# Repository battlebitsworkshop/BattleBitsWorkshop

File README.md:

### Hi there 👋

Presentation:   
http://iboibelings.nl/BattleBitsWorkshop

Wiki:   
https://github.com/battlebitsworkshop/battlebitsworkshop/wiki
  
Assembly part one:   
https://github.com/battlebitsworkshop/battlebitsworkshop/wiki/Assembly-part-one

<!--
**battlebitsworkshop/BattleBitsWorkshop** is a ✨ _special_ ✨ repository because its `README.md` (this file) appears on your GitHub profile.

Here are some ideas to get you started:

- 🔭 I’m currently working on ...
- 🌱 I’m currently learning ...
- 👯 I’m looking to collaborate on ...
- 🤔 I’m looking for help with ...
- 💬 Ask me about ...
- 📫 How to reach me: ...
- 😄 Pronouns: ...
- ⚡ Fun fact: ...
-->

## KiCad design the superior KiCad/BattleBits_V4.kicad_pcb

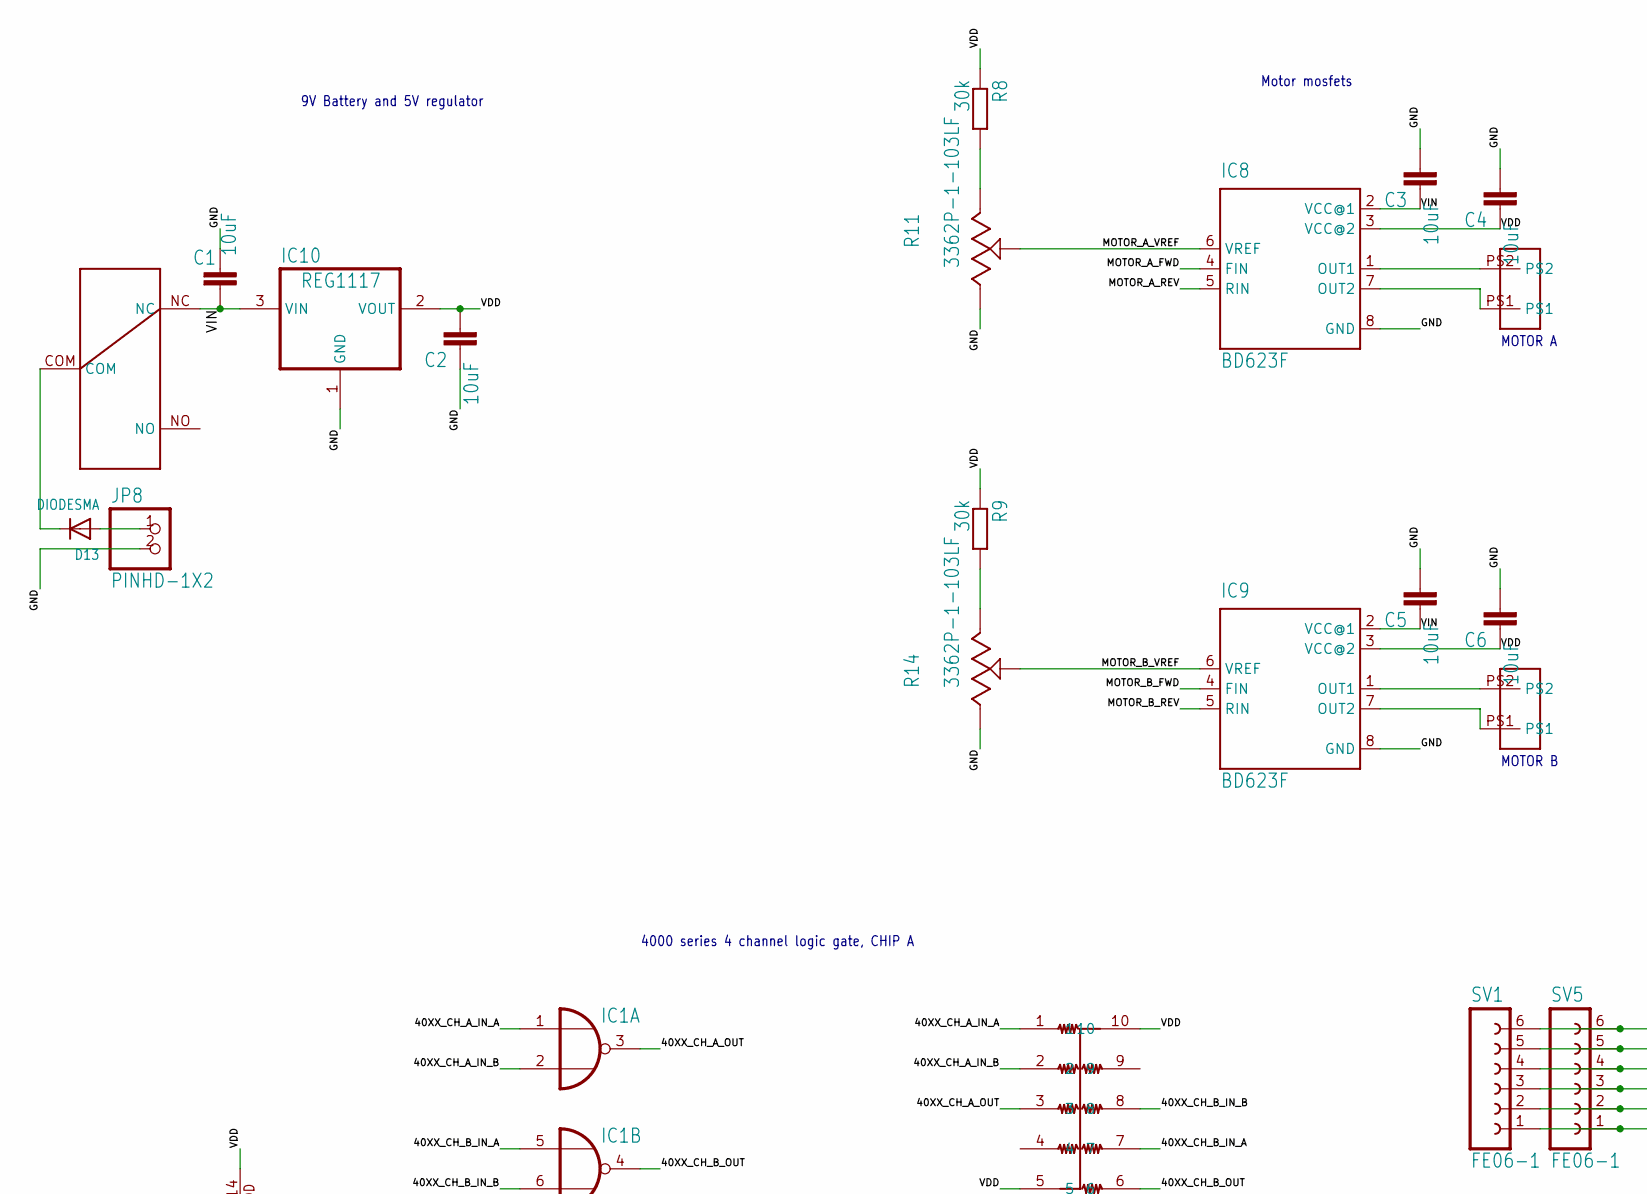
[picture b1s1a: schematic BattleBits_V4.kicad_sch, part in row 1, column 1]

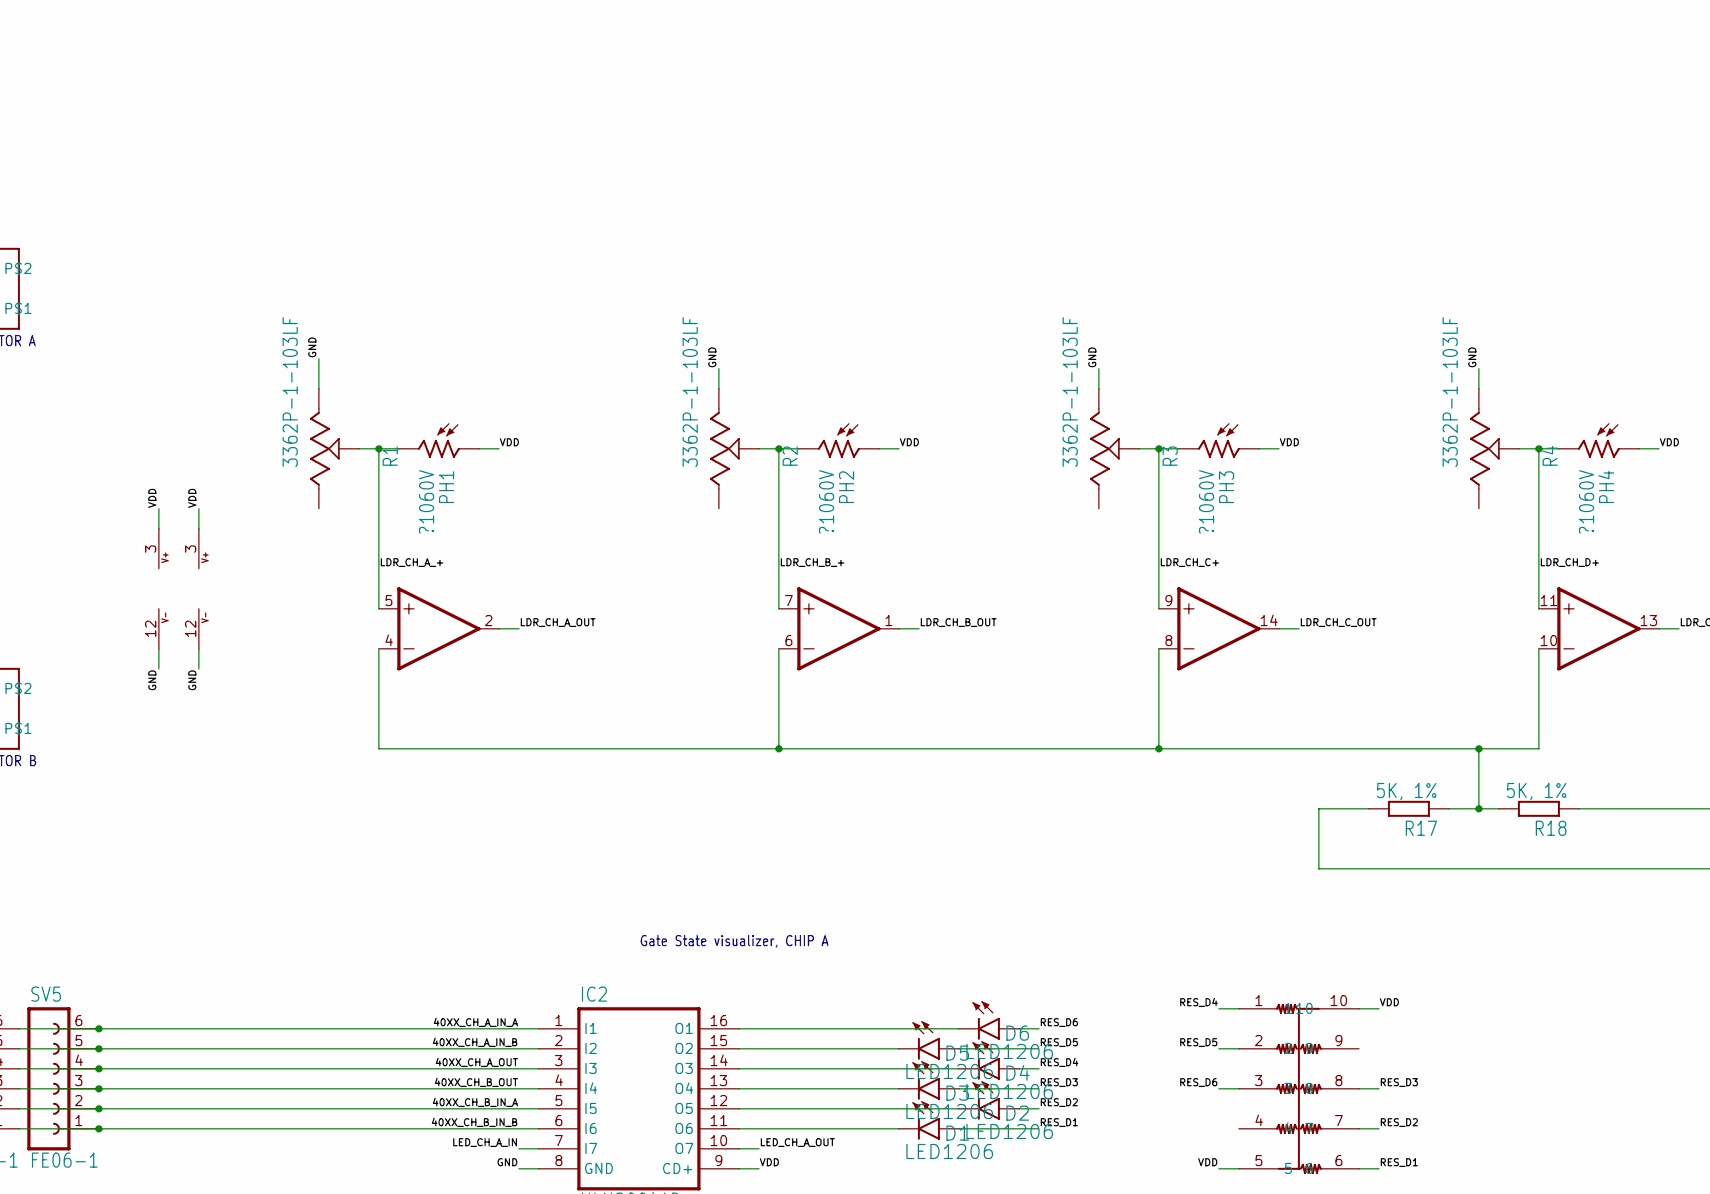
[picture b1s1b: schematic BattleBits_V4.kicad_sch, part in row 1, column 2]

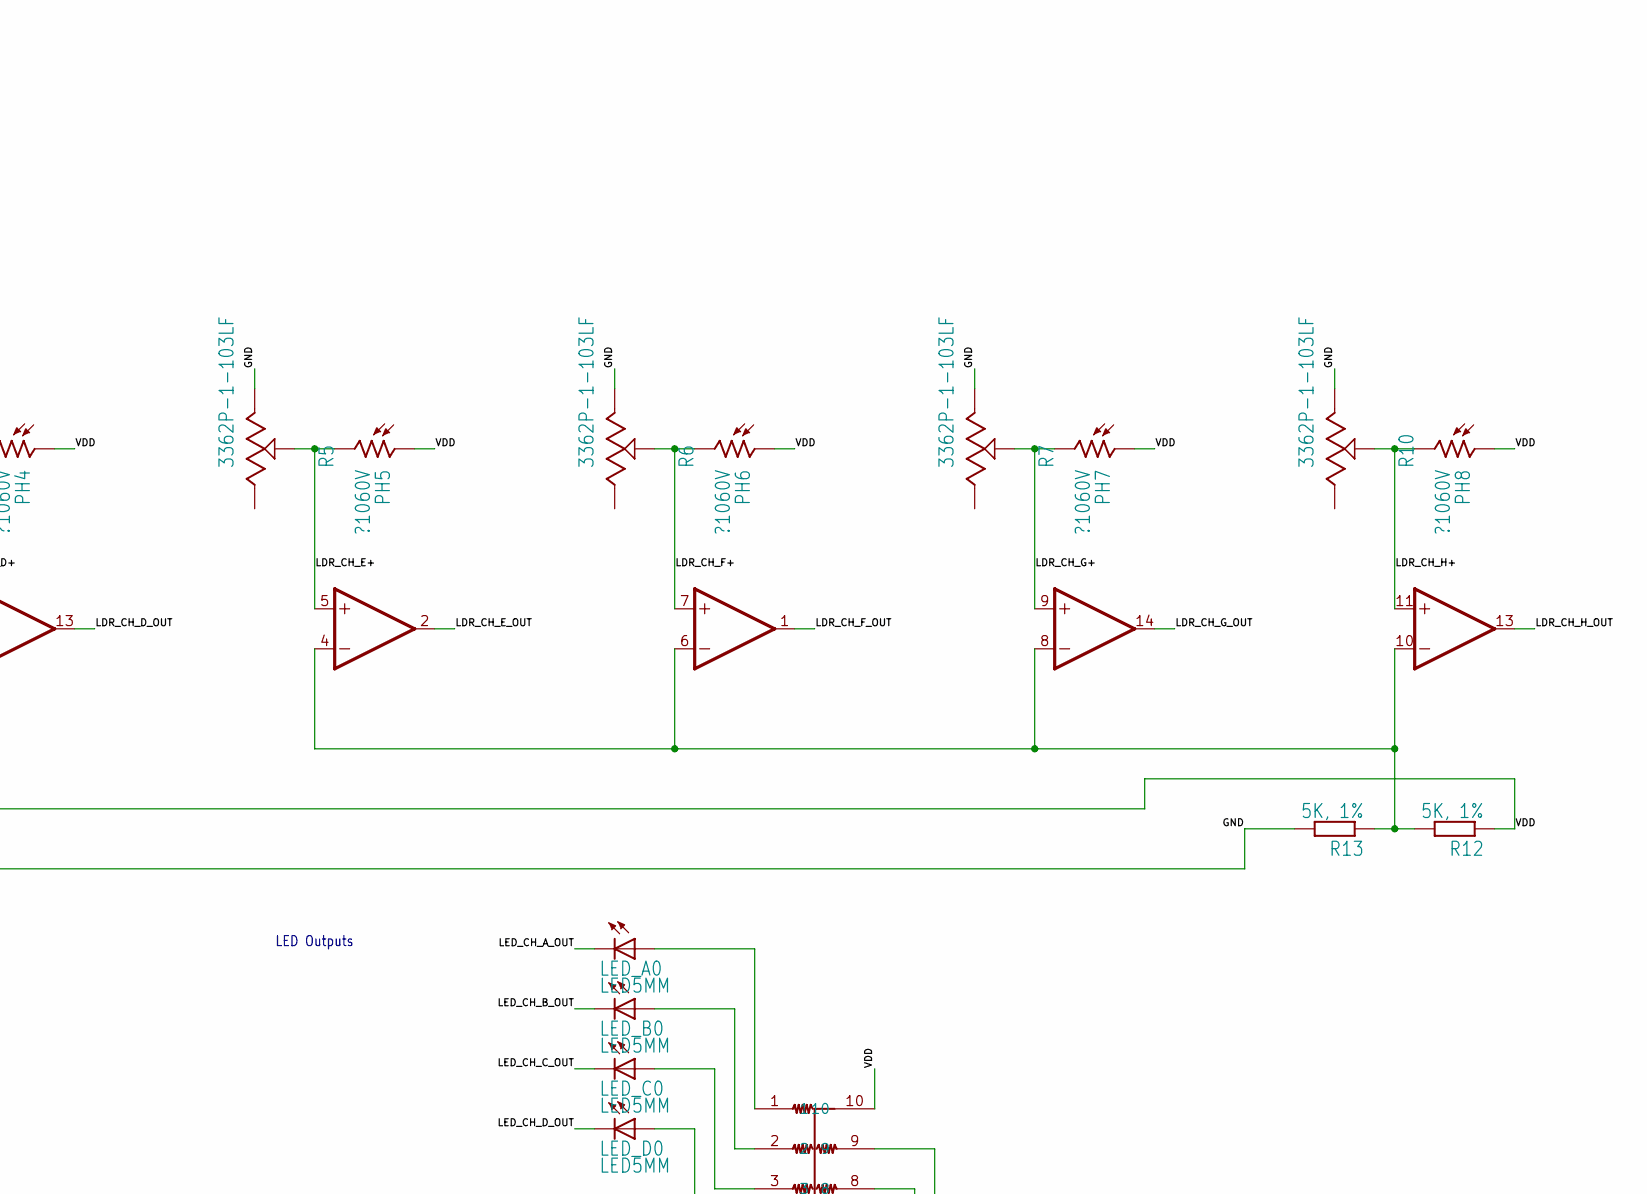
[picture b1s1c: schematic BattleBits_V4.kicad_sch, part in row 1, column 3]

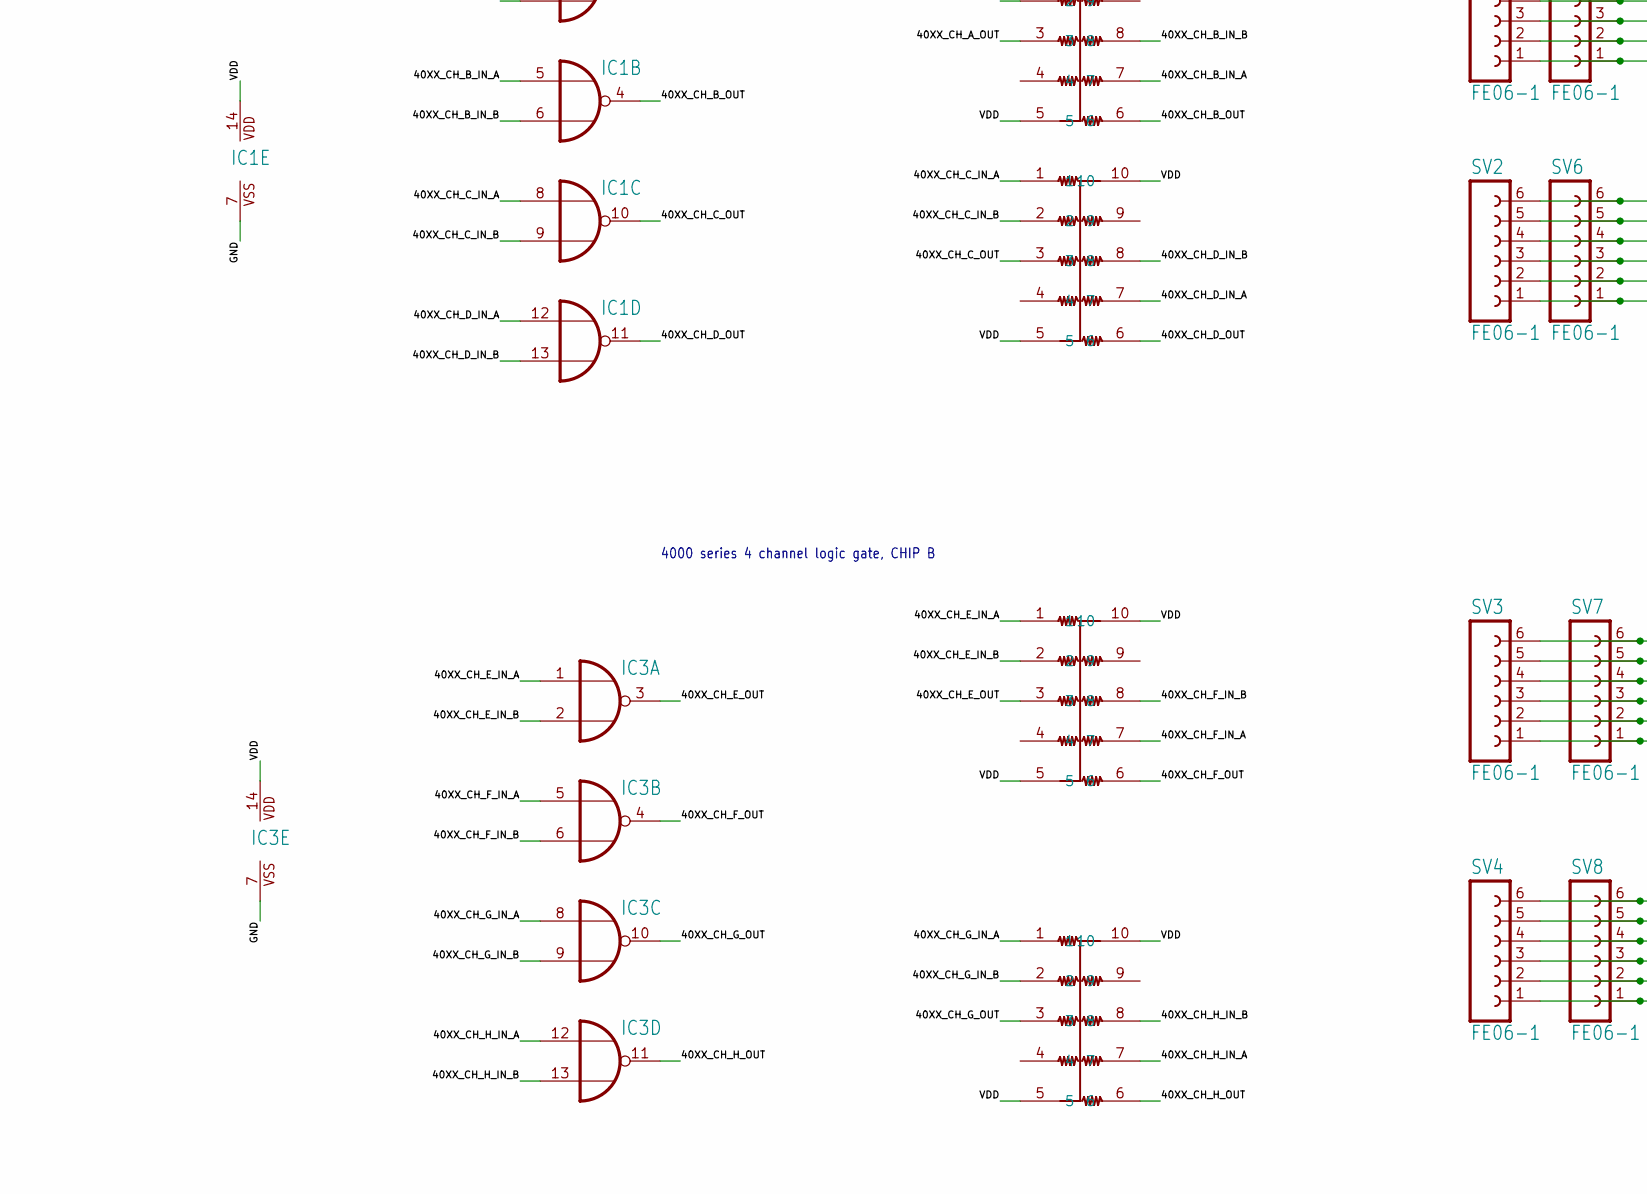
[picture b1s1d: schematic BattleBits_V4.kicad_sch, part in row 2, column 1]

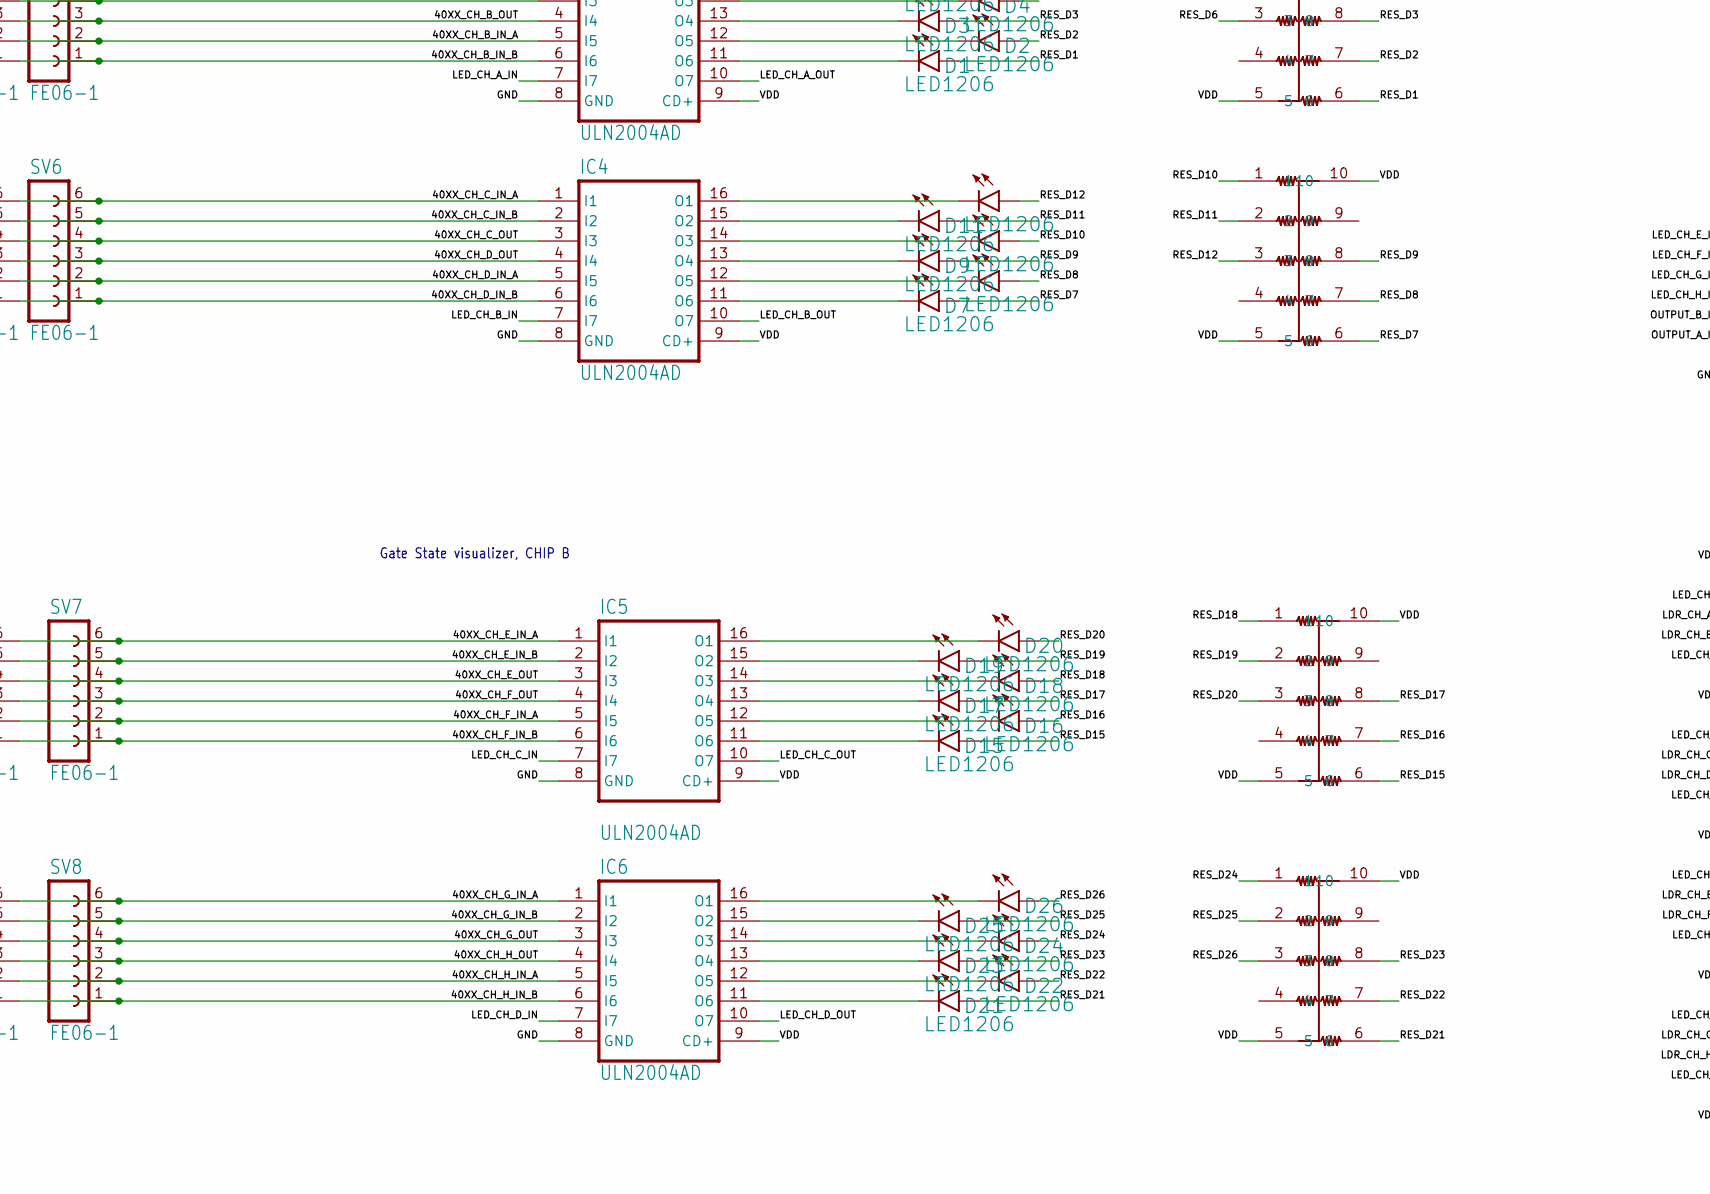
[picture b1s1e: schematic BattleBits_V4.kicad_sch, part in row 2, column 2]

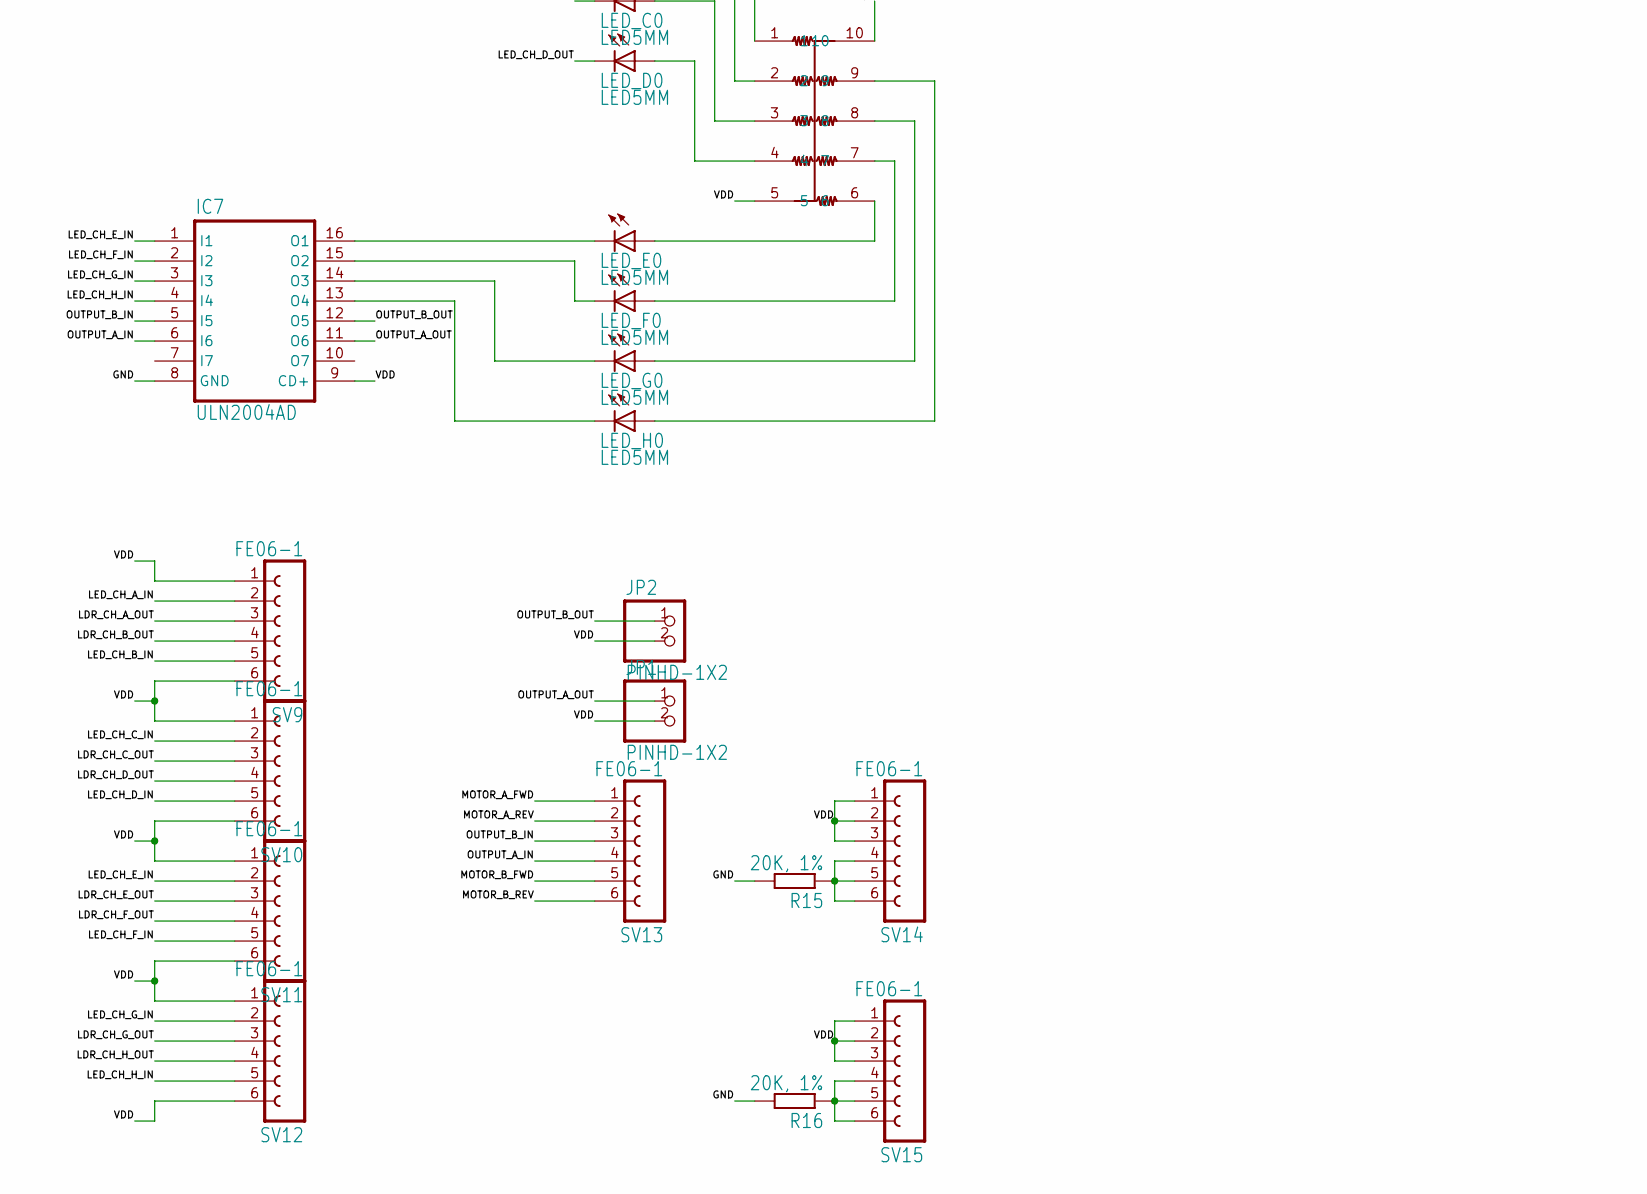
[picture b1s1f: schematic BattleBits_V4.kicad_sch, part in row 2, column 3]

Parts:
C1, C2, C3, C4, C5, C6: 10uF; C3216
D1, D2, D3, D4, D5, D6, D7, D8, D9, D10, D11, D12, D15, D16, D17, D18, D19, D20, D21, D22, D23, D24, D25, D26: LED1206; LED-1206
D13: DIODESMA; SMADIODE
IC1, IC3: 4001N; DIL14
IC2, IC4, IC5, IC6, IC7: ULN2004AD; SO16
IC8, IC9: BD623F; SOP8
IC10: REG1117; SOT223
IC11, IC12: LM2901D; SO14
JP1, JP2, JP8: PINHD-1X2; 1X02
LED_A0: LED5MM
LED_B0: LED5MM
LED_C0: LED5MM
LED_D0: LED5MM
LED_E0: LED5MM
LED_F0: LED5MM
LED_G0: LED5MM
LED_H0: LED5MM
PH1, PH2, PH3, PH4, PH5, PH6, PH7, PH8: ?1060V; TO-5_V10
R1, R2, R3, R4, R5, R6, R7, R10, R11, R14: 3362P-1-103LF
R8, R9: 30k; R3216
R12, R13, R17, R18: 5K, 1%; R3216
R15, R16: 20K, 1%; R3216
SV1, SV2, SV3, SV4, SV5, SV6, SV7, SV8, SV9, SV10, SV11, SV12, SV13, SV14, SV15: FE06-1; FE06
U$1, U$2: MOTOR; GEARMOTOR
U$3, U$5, U$6, U$9, U$10, U$11, U$19, U$20: 10K; EXBA
U$4: 330; EXBA
U$7: SLIDE_SWITCH

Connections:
/40XX_CH_A_IN_A: IC1.1 (I0), IC2.1 (I1), SV1.6, SV5.6, U$3.1
/40XX_CH_A_IN_B: IC1.2 (I1), IC2.2 (I2), SV1.5, SV5.5, U$3.2
/40XX_CH_A_OUT: IC1.3 (O), IC2.3 (I3), SV1.4, SV5.4, U$3.3
/40XX_CH_B_IN_A: IC1.5 (I0), IC2.5 (I5), SV1.2, SV5.2, U$3.7
/40XX_CH_B_IN_B: IC1.6 (I1), IC2.6 (I6), SV1.1, SV5.1, U$3.8
/40XX_CH_B_OUT: IC1.4 (O), IC2.4 (I4), SV1.3, SV5.3, U$3.6
/40XX_CH_C_IN_A: IC1.8 (I0), IC4.1 (I1), SV2.6, SV6.6, U$10.1
/40XX_CH_C_IN_B: IC1.9 (I1), IC4.2 (I2), SV2.5, SV6.5, U$10.2
/40XX_CH_C_OUT: IC1.10 (O), IC4.3 (I3), SV2.4, SV6.4, U$10.3
/40XX_CH_D_IN_A: IC1.12 (I0), IC4.5 (I5), SV2.2, SV6.2, U$10.7
/40XX_CH_D_IN_B: IC1.13 (I1), IC4.6 (I6), SV2.1, SV6.1, U$10.8
/40XX_CH_D_OUT: IC1.11 (O), IC4.4 (I4), SV2.3, SV6.3, U$10.6
/40XX_CH_E_IN_A: IC3.1 (I0), IC5.1 (I1), SV3.6, SV7.6, U$11.1
/40XX_CH_E_IN_B: IC3.2 (I1), IC5.2 (I2), SV3.5, SV7.5, U$11.2
/40XX_CH_E_OUT: IC3.3 (O), IC5.3 (I3), SV3.4, SV7.4, U$11.3
/40XX_CH_F_IN_A: IC3.5 (I0), IC5.5 (I5), SV3.2, SV7.2, U$11.7
/40XX_CH_F_IN_B: IC3.6 (I1), IC5.6 (I6), SV3.1, SV7.1, U$11.8
/40XX_CH_F_OUT: IC3.4 (O), IC5.4 (I4), SV3.3, SV7.3, U$11.6
/40XX_CH_G_IN_A: IC3.8 (I0), IC6.1 (I1), SV4.6, SV8.6, U$20.1
/40XX_CH_G_IN_B: IC3.9 (I1), IC6.2 (I2), SV4.5, SV8.5, U$20.2
/40XX_CH_G_OUT: IC3.10 (O), IC6.3 (I3), SV4.4, SV8.4, U$20.3
/40XX_CH_H_IN_A: IC3.12 (I0), IC6.5 (I5), SV4.2, SV8.2, U$20.7
/40XX_CH_H_IN_B: IC3.13 (I1), IC6.6 (I6), SV4.1, SV8.1, U$20.8
/40XX_CH_H_OUT: IC3.11 (O), IC6.4 (I4), SV4.3, SV8.3, U$20.6
/GND: C1.1, C2.1, C3.2, C4.2, C5.2, C6.2, IC1.7 (VSS), IC2.8 (GND), IC3.7 (VSS), IC4.8 (GND), IC5.8 (GND), IC6.8 (GND), IC7.8 (GND), IC8.8 (GND), IC9.8 (GND), IC10.1 (GND), IC11.12 (V-), IC12.12 (V-), JP8.2, R1.1, R2.1, R3.1, R4.1, R5.1, R6.1, R7.1, R10.1, R11.3, R13.2, R14.3, R15.2, R16.2, R17.2
/LDR_CH_A_+: IC11.5 (+IN), PH1.2, R1.2
/LDR_CH_A_OUT: IC11.2 (OUT), SV9.3
/LDR_CH_B_+: IC11.7 (+IN), PH2.2, R2.2
/LDR_CH_B_OUT: IC11.1 (OUT), SV9.4
/LDR_CH_C+: IC11.9 (+IN), PH3.2, R3.2
/LDR_CH_C_OUT: IC11.14 (OUT), SV10.3
/LDR_CH_D+: IC11.11 (+IN), PH4.2, R4.2
/LDR_CH_D_OUT: IC11.13 (OUT), SV10.4
/LDR_CH_E+: IC12.5 (+IN), PH5.2, R5.2
/LDR_CH_E_OUT: IC12.2 (OUT), SV11.3
/LDR_CH_F+: IC12.7 (+IN), PH6.2, R6.2
/LDR_CH_F_OUT: IC12.1 (OUT), SV11.4
/LDR_CH_G+: IC12.9 (+IN), PH7.2, R7.2
/LDR_CH_G_OUT: IC12.14 (OUT), SV12.3
/LDR_CH_H+: IC12.11 (+IN), PH8.2, R10.2
/LDR_CH_H_OUT: IC12.13 (OUT), SV12.4
/LED_CH_A_IN: IC2.7 (I7), SV9.2
/LED_CH_A_OUT: IC2.10 (O7), LED_A0.K (C)
/LED_CH_B_IN: IC4.7 (I7), SV9.5
/LED_CH_B_OUT: IC4.10 (O7), LED_B0.K (C)
/LED_CH_C_IN: IC5.7 (I7), SV10.2
/LED_CH_C_OUT: IC5.10 (O7), LED_C0.K (C)
/LED_CH_D_IN: IC6.7 (I7), SV10.5
/LED_CH_D_OUT: IC6.10 (O7), LED_D0.K (C)
/LED_CH_E_IN: IC7.1 (I1), SV11.2
/LED_CH_F_IN: IC7.2 (I2), SV11.5
/LED_CH_G_IN: IC7.3 (I3), SV12.2
/LED_CH_H_IN: IC7.4 (I4), SV12.5
/MOTOR_A_FWD: IC8.4 (FIN), SV13.1
/MOTOR_A_REV: IC8.5 (RIN), SV13.2
/MOTOR_A_VREF: IC8.6 (VREF), R11.2
/MOTOR_B_FWD: IC9.4 (FIN), SV13.5
/MOTOR_B_REV: IC9.5 (RIN), SV13.6
/MOTOR_B_VREF: IC9.6 (VREF), R14.2
/OUTPUT_A_IN: IC7.6 (I6), SV13.4
/OUTPUT_A_OUT: IC7.11 (O6), JP1.1
/OUTPUT_B_IN: IC7.5 (I5), SV13.3
/OUTPUT_B_OUT: IC7.12 (O5), JP2.1
/RES_D1: D1.A, U$19.6
/RES_D2: D2.A, U$19.7
/RES_D3: D3.A, U$19.8
/RES_D4: D4.A, U$19.1
/RES_D5: D5.A, U$19.2
/RES_D6: D6.A, U$19.3
/RES_D7: D7.A, U$5.6
/RES_D8: D8.A, U$5.7
/RES_D9: D9.A, U$5.8
/RES_D10: D10.A, U$5.1
/RES_D11: D11.A, U$5.2
/RES_D12: D12.A, U$5.3
/RES_D15: D15.A, U$6.6
/RES_D16: D16.A, U$6.7
/RES_D17: D17.A, U$6.8
/RES_D18: D18.A, U$6.1
/RES_D19: D19.A, U$6.2
/RES_D20: D20.A, U$6.3
/RES_D21: D21.A, U$9.6
/RES_D22: D22.A, U$9.7
/RES_D23: D23.A, U$9.8
/RES_D24: D24.A, U$9.1
/RES_D25: D25.A, U$9.2
/RES_D26: D26.A, U$9.3
/VDD: C2.2, C4.1, C6.1, IC1.14 (VDD), IC2.9 (CD+), IC3.14 (VDD), IC4.9 (CD+), IC5.9 (CD+), IC6.9 (CD+), IC7.9 (CD+), IC8.3 (VCC@2), IC9.3 (VCC@2), IC10.2 (VOUT), IC11.3 (V+), IC12.3 (V+), JP1.2, JP2.2, PH1.1, PH2.1, PH3.1, PH4.1, PH5.1, PH6.1, PH7.1, PH8.1, R8.1, R9.1, R12.1, R18.1, SV9.1, SV9.6, SV10.1, SV10.6, SV11.1, SV11.6, SV12.1, SV12.6, SV14.1, SV14.2, SV14.3, SV15.1, SV15.2, SV15.3, U$3.5, U$3.10, U$4.5, U$4.10, U$5.5, U$5.10, U$6.5, U$6.10, U$9.5, U$9.10, U$10.5, U$10.10, U$11.5, U$11.10, U$19.5, U$19.10, U$20.5, U$20.10
/VIN: C1.2, C3.1, C5.1, IC8.2 (VCC@1), IC9.2 (VCC@1), IC10.3 (VIN), U$7.NC
unnamed: D1.C, IC2.11 (O6)
unnamed: D2.C, IC2.12 (O5)
unnamed: D3.C, IC2.13 (O4)
unnamed: D4.C, IC2.14 (O3)
unnamed: D5.C, IC2.15 (O2)
unnamed: D6.C, IC2.16 (O1)
unnamed: D7.C, IC4.11 (O6)
unnamed: D8.C, IC4.12 (O5)
unnamed: D9.C, IC4.13 (O4)
unnamed: D10.C, IC4.14 (O3)
unnamed: D11.C, IC4.15 (O2)
unnamed: D12.C, IC4.16 (O1)
unnamed: D13.A, JP8.1
unnamed: D13.C, U$7.COM
unnamed: D15.C, IC5.11 (O6)
unnamed: D16.C, IC5.12 (O5)
unnamed: D17.C, IC5.13 (O4)
unnamed: D18.C, IC5.14 (O3)
unnamed: D19.C, IC5.15 (O2)
unnamed: D20.C, IC5.16 (O1)
unnamed: D21.C, IC6.11 (O6)
unnamed: D22.C, IC6.12 (O5)
unnamed: D23.C, IC6.13 (O4)
unnamed: D24.C, IC6.14 (O3)
unnamed: D25.C, IC6.15 (O2)
unnamed: D26.C, IC6.16 (O1)
unnamed: IC7.13 (O4), LED_H0.K (C)
unnamed: IC7.14 (O3), LED_G0.K (C)
unnamed: IC7.15 (O2), LED_F0.K (C)
unnamed: IC7.16 (O1), LED_E0.K (C)
unnamed: IC8.1 (OUT1), U$1.P$2
unnamed: IC8.7 (OUT2), U$1.P$1
unnamed: IC9.1 (OUT1), U$2.P$2
unnamed: IC9.7 (OUT2), U$2.P$1
unnamed: IC11.4 (-IN), IC11.6 (-IN), IC11.8 (-IN), IC11.10 (-IN), R17.1, R18.2
unnamed: IC12.4 (-IN), IC12.6 (-IN), IC12.8 (-IN), IC12.10 (-IN), R12.2, R13.1
unnamed: LED_A0.A, U$4.1
unnamed: LED_B0.A, U$4.2
unnamed: LED_C0.A, U$4.3
unnamed: LED_D0.A, U$4.4
unnamed: LED_E0.A, U$4.6
unnamed: LED_F0.A, U$4.7
unnamed: LED_G0.A, U$4.8
unnamed: LED_H0.A, U$4.9
unnamed: R8.2, R11.1
unnamed: R9.2, R14.1
unnamed: R15.1, SV14.4, SV14.5, SV14.6
unnamed: R16.1, SV15.4, SV15.5, SV15.6

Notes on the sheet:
Gate State visualizer, CHIP A
MOTOR B
Motor mosfets
9V Battery and 5V regulator
LED Outputs
4000 series 4 channel logic gate, CHIP A
4000 series 4 channel logic gate, CHIP B
Gate State visualizer, CHIP B
MOTOR A

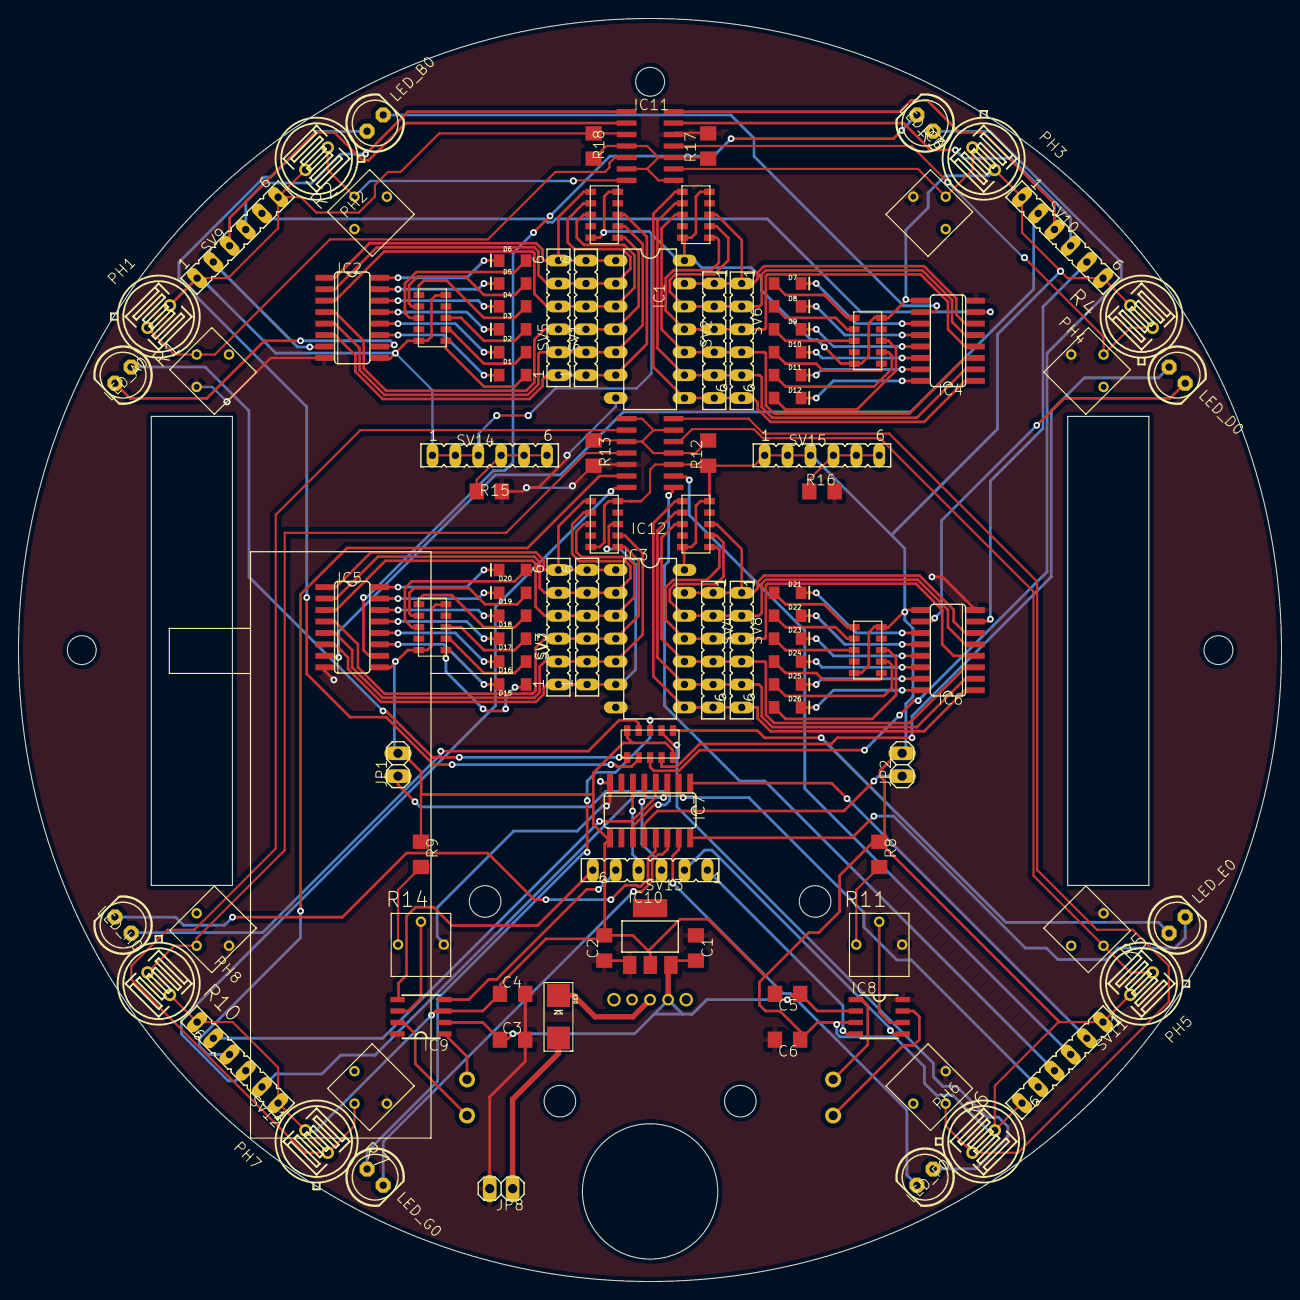
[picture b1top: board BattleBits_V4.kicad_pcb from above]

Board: 2 copper layers, 140.0 x 140.0 mm, 113 parts (1 on the bottom side), 137 nets.

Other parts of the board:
@HOLE0, @HOLE1, @HOLE2, @HOLE3, @HOLE4, @HOLE5: (no value)

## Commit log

2021-09-02 added dxf
2022-09-05 eagle added
2022-09-05 kicad
2022-09-06 silkscreen added
2022-09-07 gerber
2022-09-27 added sticker
